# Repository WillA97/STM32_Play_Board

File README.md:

# STM32_Play_Board
 schematic of the microcontroller pcb files

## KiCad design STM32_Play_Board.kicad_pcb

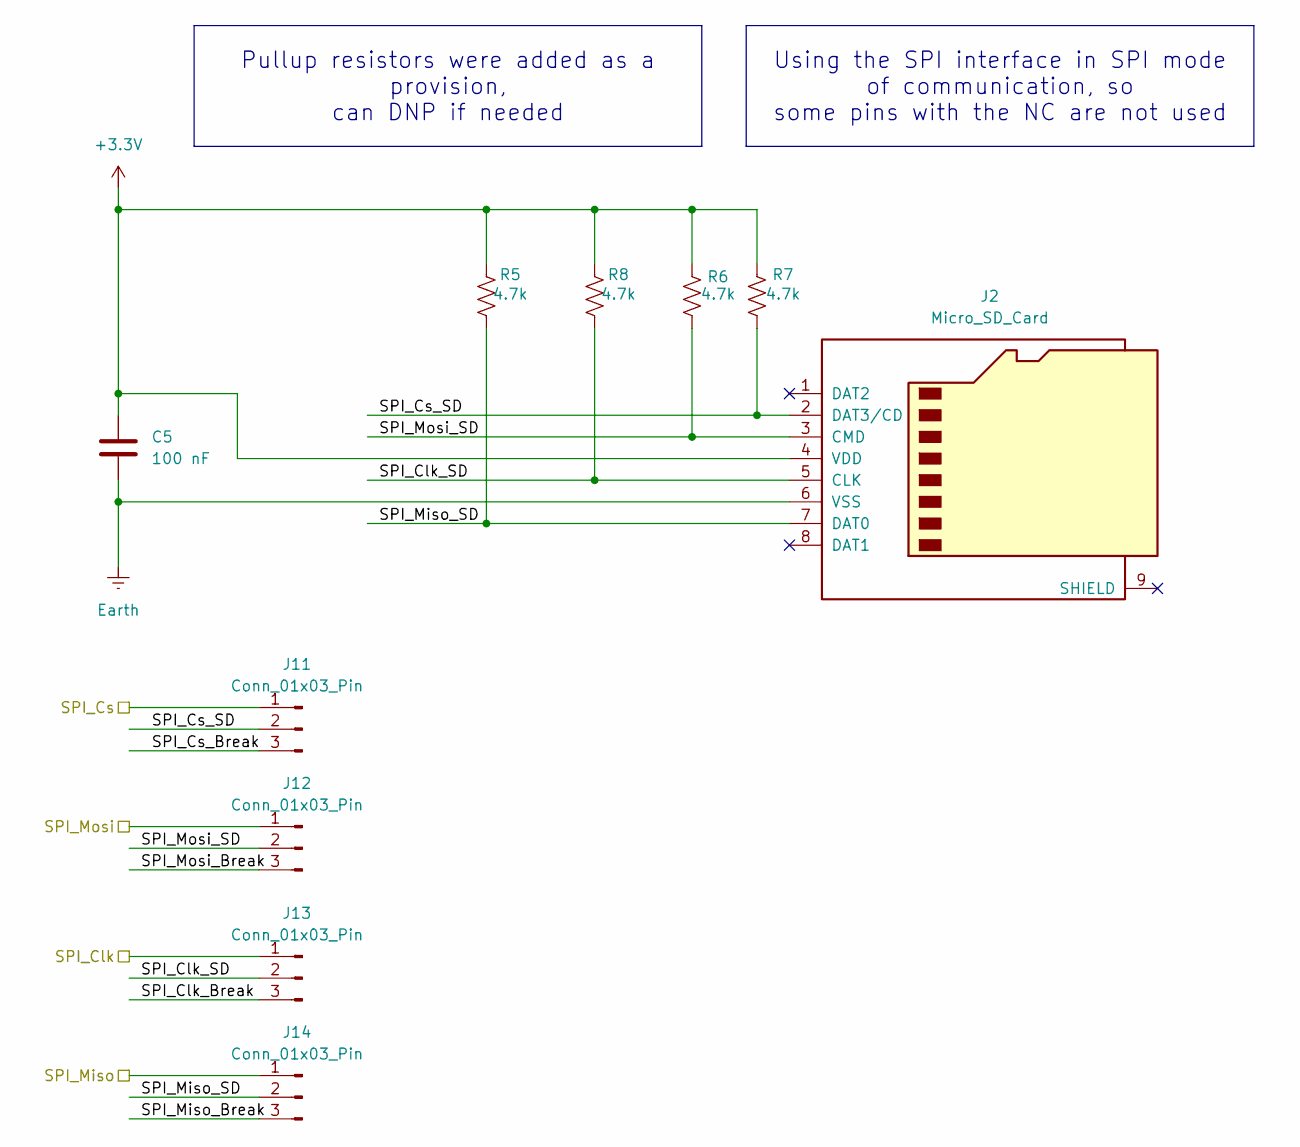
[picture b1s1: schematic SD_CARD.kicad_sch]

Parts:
C5: 100 nF; C_0805_2012Metric
J2: Micro_SD_Card; microSD_HC_Molex_104031-0811
J11, J12, J13, J14: Conn_01x03_Pin; PinHeader_1x03_P2.54mm_Vertical
R5, R6, R7, R8: 4.7k; R_0805_2012Metric

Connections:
+3.3V: C5.1, J2.4 (VDD), R5.1, R6.1, R7.1, R8.1; also elsewhere on the board
/Micrcontroller STM32C0/SPI_Clk: J13.1; also elsewhere on the board
/Micrcontroller STM32C0/SPI_Cs: J11.1; also elsewhere on the board
/Micrcontroller STM32C0/SPI_Miso: J14.1; also elsewhere on the board
/Micrcontroller STM32C0/SPI_Mosi: J12.1; also elsewhere on the board
/SD_CARD/SPI_Clk_Break: J13.3
/SD_CARD/SPI_Clk_SD: J2.5 (CLK), J13.2, R8.2
/SD_CARD/SPI_Cs_Break: J11.3
/SD_CARD/SPI_Cs_SD: J2.2 (DAT3/CD), J11.2, R7.2
/SD_CARD/SPI_Miso_Break: J14.3
/SD_CARD/SPI_Miso_SD: J2.7 (DAT0), J14.2, R5.2
/SD_CARD/SPI_Mosi_Break: J12.3
/SD_CARD/SPI_Mosi_SD: J2.3 (CMD), J12.2, R6.2
Earth: C5.2, J2.6 (VSS); also elsewhere on the board

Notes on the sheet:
Using the SPI interface in SPI mode of communication, so some pins with the NC are not used
Pullup resistors were added as a provision, can DNP if needed

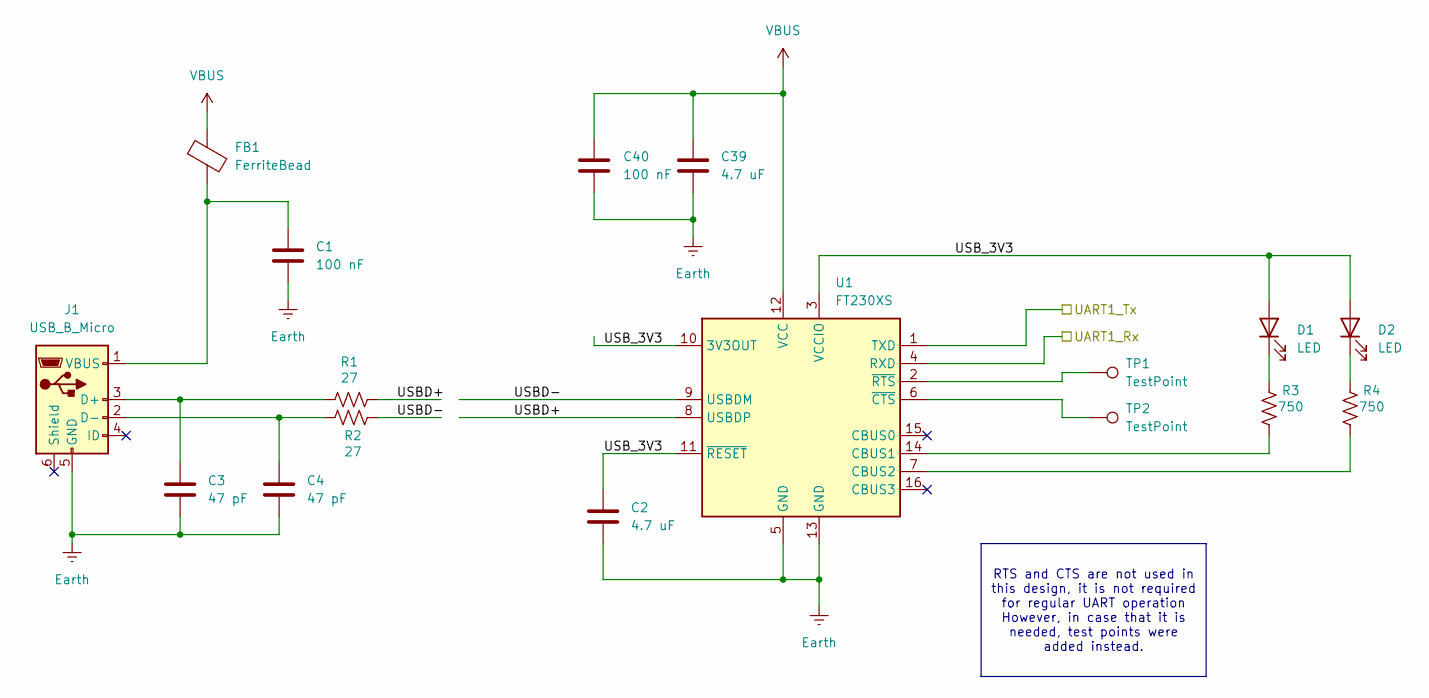
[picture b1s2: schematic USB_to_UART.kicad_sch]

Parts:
C1, C40: 100 nF; C_0805_2012Metric
C2, C39: 4.7 uF; C_0805_2012Metric
C3, C4: 47 pF; C_0805_2012Metric
D1, D2: LED; LED_0805_2012Metric
FB1: FerriteBead; L_0805_2012Metric
J1: USB_B_Micro; USB_Micro-B_Wuerth_629105150521
R1, R2: 27; R_0805_2012Metric
R3, R4: 750; R_0805_2012Metric
TP1, TP2: TestPoint; TestPoint_Pad_2.0x2.0mm
U1: FT230XS; SSOP-16_3.9x4.9mm_P0.635mm

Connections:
/Micrcontroller STM32C0/UART1_Rx: U1.4 (RXD); also elsewhere on the board
/Micrcontroller STM32C0/UART1_Tx: U1.1 (TXD); also elsewhere on the board
/USB to UART/USBD+: R1.2, U1.8 (USBDP)
/USB to UART/USBD-: R2.2, U1.9 (USBDM)
/USB to UART/USB_3V3: C2.1, D1.2 (A), D2.2 (A), U1.3 (VCCIO), U1.10 (3V3OUT), U1.11 (~RESET)
Earth: C1.2, C2.2, C3.2, C4.2, C39.2, C40.2, J1.5 (GND), U1.5 (GND), U1.13 (GND); also elsewhere on the board
unnamed: D1.1 (K), R3.1
unnamed: D2.1 (K), R4.1
unnamed: C3.1, J1.3 (D+), R1.1
unnamed: C4.1, J1.2 (D-), R2.1
unnamed: C1.1, FB1.2, J1.1 (VBUS)
unnamed: R3.2, U1.14 (CBUS1)
unnamed: R4.2, U1.7 (CBUS2)
unnamed: TP2.1, U1.6 (~CTS)
unnamed: TP1.1, U1.2 (~RTS)
VBUS: C39.1, C40.1, FB1.1, U1.12 (VCC); also elsewhere on the board

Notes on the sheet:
RTS and CTS are not used in this design, it is not required for regular UART operation However, in case that it is needed, test points were added instead.

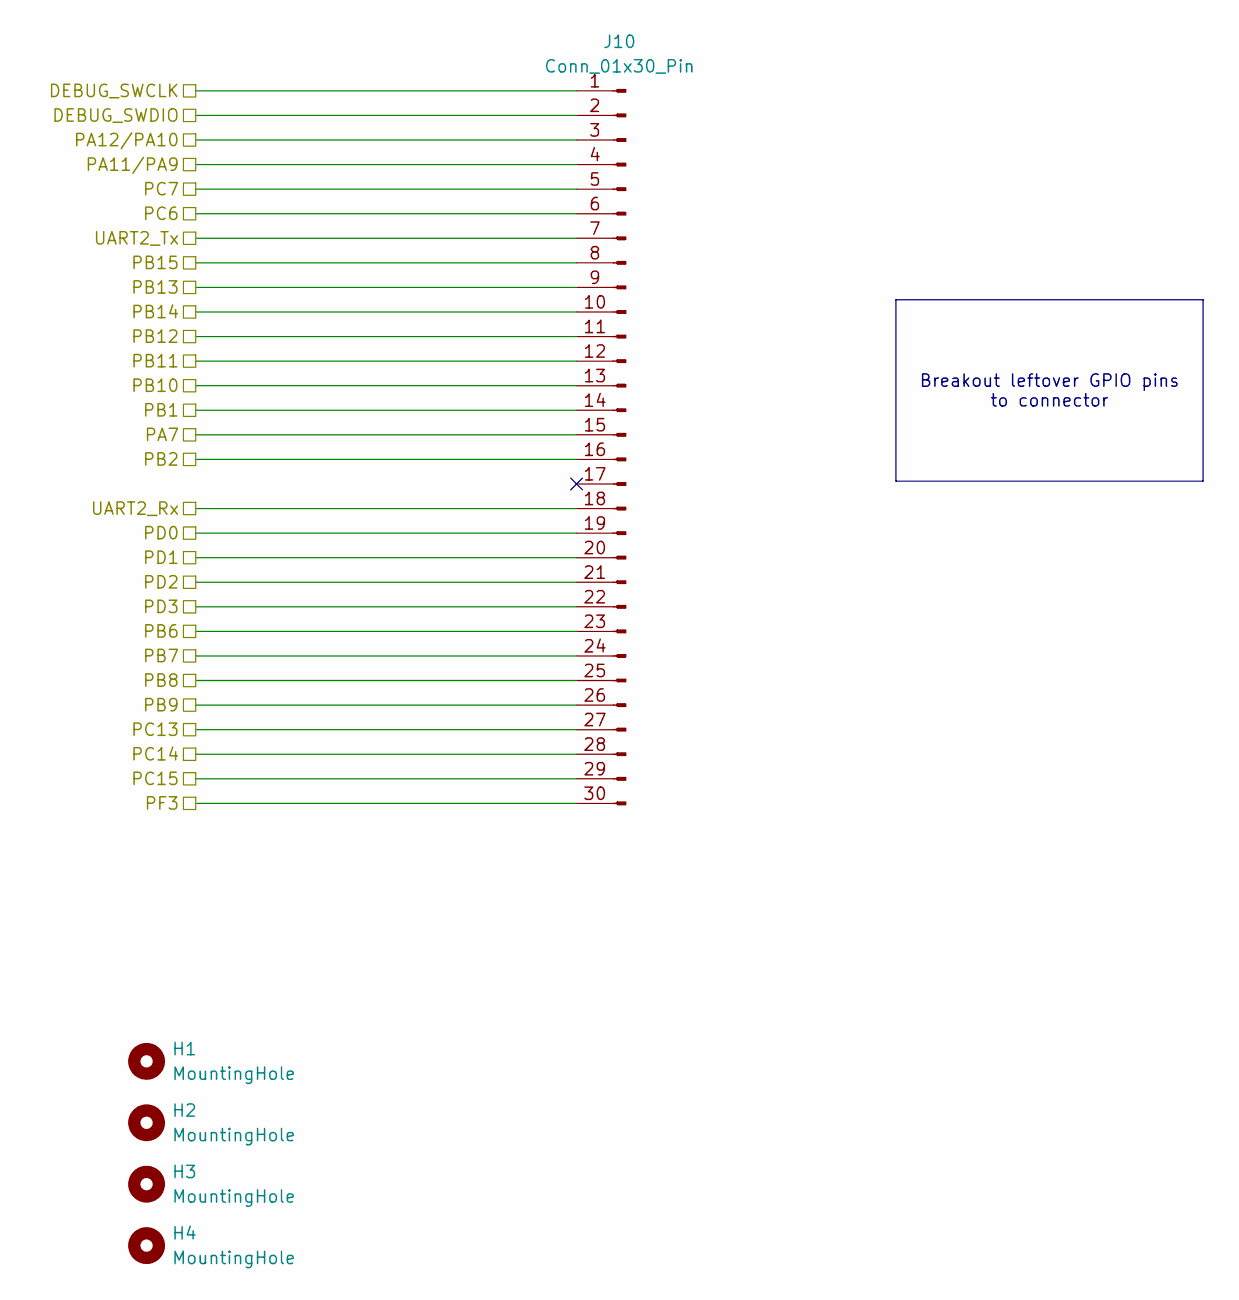
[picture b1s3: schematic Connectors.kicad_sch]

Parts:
H1, H2, H3, H4: MountingHole; MountingHole_3.2mm_M3
J10: Conn_01x30_Pin; PinHeader_1x30_P2.54mm_Vertical

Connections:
/Connectors/DEBUG_SWCLK: J10.1; also elsewhere on the board
/Connectors/DEBUG_SWDIO: J10.2; also elsewhere on the board
/Connectors/PA7: J10.15; also elsewhere on the board
/Connectors/PA11/PA9: J10.4; also elsewhere on the board
/Connectors/PA12/PA10: J10.3; also elsewhere on the board
/Connectors/PB1: J10.14; also elsewhere on the board
/Connectors/PB2: J10.16; also elsewhere on the board
/Connectors/PB6: J10.23; also elsewhere on the board
/Connectors/PB7: J10.24; also elsewhere on the board
/Connectors/PB8: J10.25; also elsewhere on the board
/Connectors/PB9: J10.26; also elsewhere on the board
/Connectors/PB10: J10.13; also elsewhere on the board
/Connectors/PB11: J10.12; also elsewhere on the board
/Connectors/PB12: J10.11; also elsewhere on the board
/Connectors/PB13: J10.9; also elsewhere on the board
/Connectors/PB14: J10.10; also elsewhere on the board
/Connectors/PB15: J10.8; also elsewhere on the board
/Connectors/PC6: J10.6; also elsewhere on the board
/Connectors/PC7: J10.5; also elsewhere on the board
/Connectors/PC13: J10.27; also elsewhere on the board
/Connectors/PC14: J10.28; also elsewhere on the board
/Connectors/PC15: J10.29; also elsewhere on the board
/Connectors/PD0: J10.19; also elsewhere on the board
/Connectors/PD1: J10.20; also elsewhere on the board
/Connectors/PD2: J10.21; also elsewhere on the board
/Connectors/PD3: J10.22; also elsewhere on the board
/Connectors/PF3: J10.30; also elsewhere on the board
/Micrcontroller STM32C0/UART2_Rx: J10.18; also elsewhere on the board
/Micrcontroller STM32C0/UART2_Tx: J10.7; also elsewhere on the board

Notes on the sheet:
Breakout leftover GPIO pins to connector

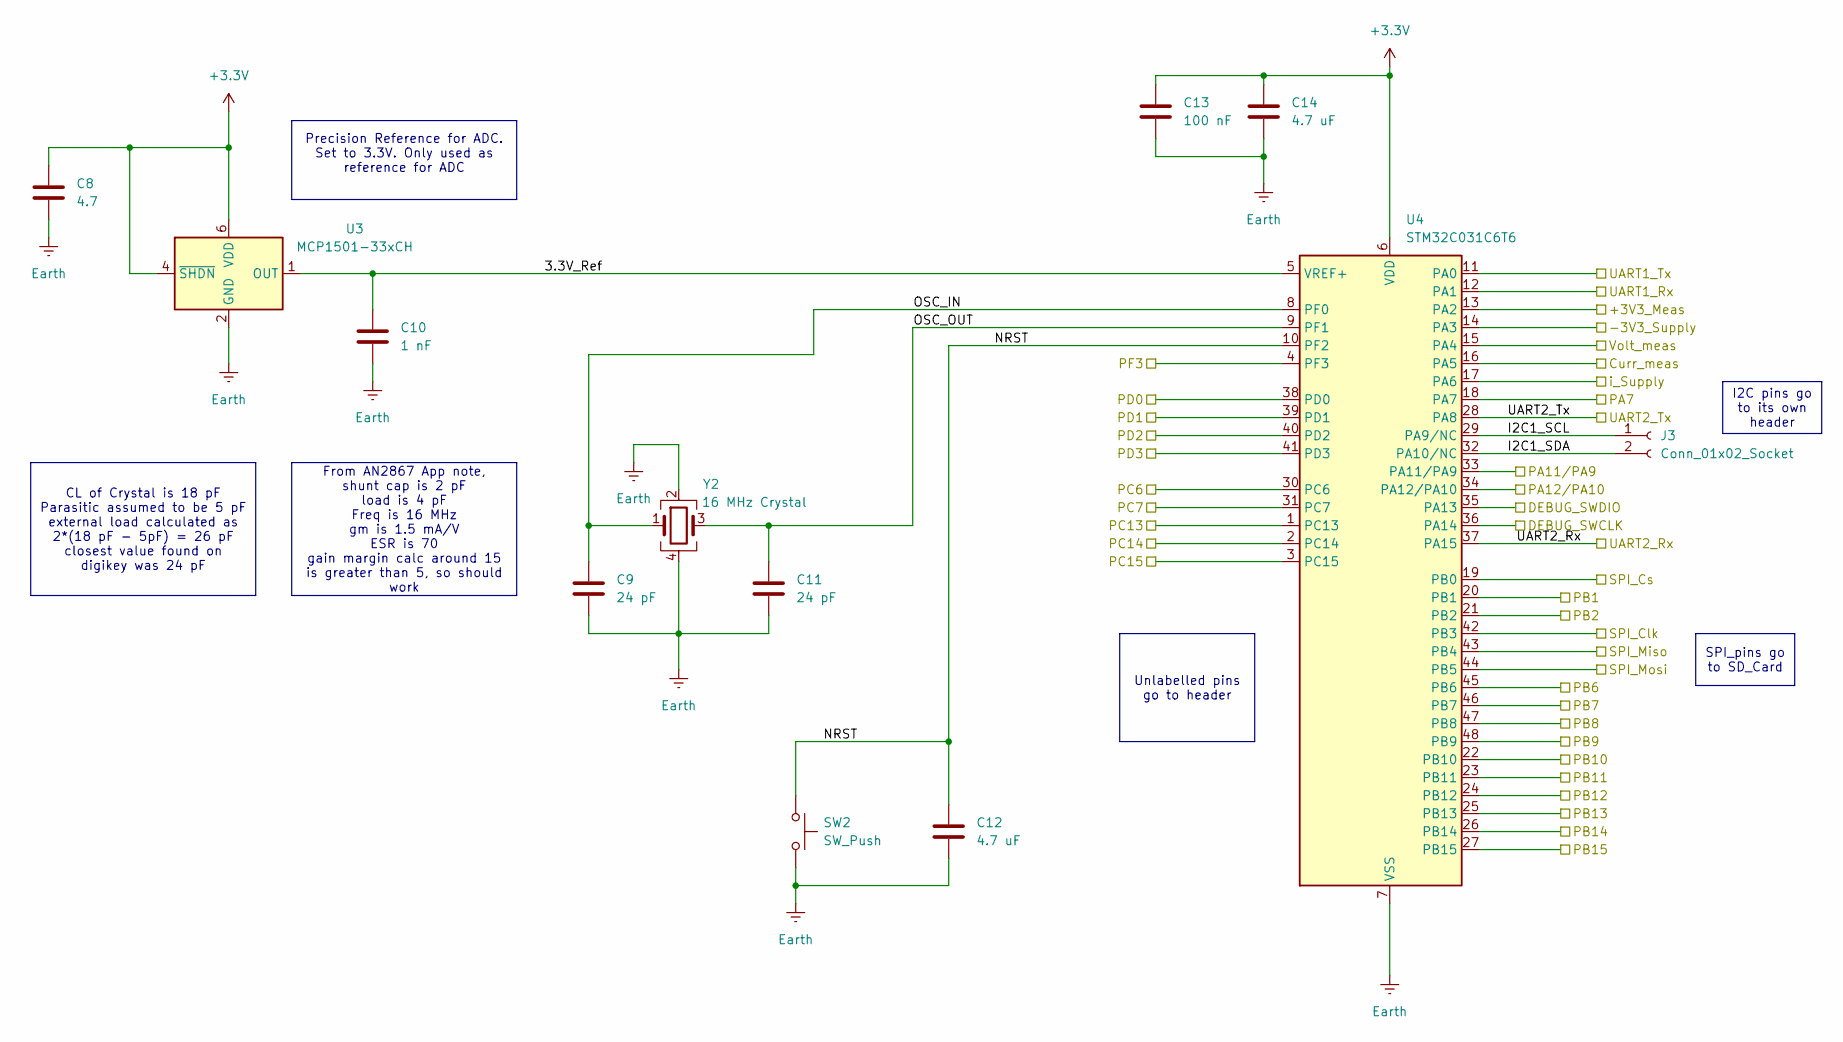
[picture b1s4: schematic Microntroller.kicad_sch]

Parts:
C8: 4.7; C_0805_2012Metric
C9, C11: 24 pF; C_0805_2012Metric
C10: 1 nF; C_0805_2012Metric
C12, C14: 4.7 uF; C_0805_2012Metric
C13: 100 nF; C_0805_2012Metric
J3: Conn_01x02_Socket; Molex_KK-254_AE-6410-02A_1x02_P2.54mm_Vertical
SW2: SW_Push; SW_PUSH_6mm
U3: MCP1501-33xCH; SOT-23-6
U4: STM32C031C6T6; LQFP-48_7x7mm_P0.5mm
Y2: 16 MHz Crystal; Oscillator_SMD_Abracon_ASE-4Pin_3.2x2.5mm_HandSoldering

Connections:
+3.3V: C8.1, C13.1, C14.1, U3.4 (~SHDN), U3.6 (VDD), U4.6 (VDD); also elsewhere on the board
/Connectors/DEBUG_SWCLK: U4.36 (PA14); also elsewhere on the board
/Connectors/DEBUG_SWDIO: U4.35 (PA13); also elsewhere on the board
/Connectors/PA7: U4.18 (PA7); also elsewhere on the board
/Connectors/PA11/PA9: U4.33 (PA11/PA9); also elsewhere on the board
/Connectors/PA12/PA10: U4.34 (PA12/PA10); also elsewhere on the board
/Connectors/PB1: U4.20 (PB1); also elsewhere on the board
/Connectors/PB2: U4.21 (PB2); also elsewhere on the board
/Connectors/PB6: U4.45 (PB6); also elsewhere on the board
/Connectors/PB7: U4.46 (PB7); also elsewhere on the board
/Connectors/PB8: U4.47 (PB8); also elsewhere on the board
/Connectors/PB9: U4.48 (PB9); also elsewhere on the board
/Connectors/PB10: U4.22 (PB10); also elsewhere on the board
/Connectors/PB11: U4.23 (PB11); also elsewhere on the board
/Connectors/PB12: U4.24 (PB12); also elsewhere on the board
/Connectors/PB13: U4.26 (PB14); also elsewhere on the board
/Connectors/PB14: U4.25 (PB13); also elsewhere on the board
/Connectors/PB15: U4.27 (PB15); also elsewhere on the board
/Connectors/PC6: U4.30 (PC6); also elsewhere on the board
/Connectors/PC7: U4.31 (PC7); also elsewhere on the board
/Connectors/PC13: U4.1 (PC13); also elsewhere on the board
/Connectors/PC14: U4.2 (PC14); also elsewhere on the board
/Connectors/PC15: U4.3 (PC15); also elsewhere on the board
/Connectors/PD0: U4.38 (PD0); also elsewhere on the board
/Connectors/PD1: U4.39 (PD1); also elsewhere on the board
/Connectors/PD2: U4.40 (PD2); also elsewhere on the board
/Connectors/PD3: U4.41 (PD3); also elsewhere on the board
/Connectors/PF3: U4.4 (PF3); also elsewhere on the board
/Micrcontroller STM32C0/3.3V_Ref: C10.1, U3.1 (OUT), U4.5 (VREF+)
/Micrcontroller STM32C0/+3V3_Meas: U4.13 (PA2); also elsewhere on the board
/Micrcontroller STM32C0/-3V3_Supply: U4.14 (PA3); also elsewhere on the board
/Micrcontroller STM32C0/Curr_meas: U4.16 (PA5); also elsewhere on the board
/Micrcontroller STM32C0/I2C1_SCL: J3.1, U4.29 (PA9/NC)
/Micrcontroller STM32C0/I2C1_SDA: J3.2, U4.32 (PA10/NC)
/Micrcontroller STM32C0/NRST: C12.1, SW2.1, U4.10 (PF2)
/Micrcontroller STM32C0/OSC_IN: C9.1, U4.8 (PF0), Y2.1
/Micrcontroller STM32C0/OSC_OUT: C11.1, U4.9 (PF1), Y2.3
/Micrcontroller STM32C0/SPI_Clk: U4.42 (PB3); also elsewhere on the board
/Micrcontroller STM32C0/SPI_Cs: U4.19 (PB0); also elsewhere on the board
/Micrcontroller STM32C0/SPI_Miso: U4.43 (PB4); also elsewhere on the board
/Micrcontroller STM32C0/SPI_Mosi: U4.44 (PB5); also elsewhere on the board
/Micrcontroller STM32C0/UART1_Rx: U4.12 (PA1); also elsewhere on the board
/Micrcontroller STM32C0/UART1_Tx: U4.11 (PA0); also elsewhere on the board
/Micrcontroller STM32C0/UART2_Rx: U4.37 (PA15); also elsewhere on the board
/Micrcontroller STM32C0/UART2_Tx: U4.28 (PA8); also elsewhere on the board
/Micrcontroller STM32C0/Volt_meas: U4.15 (PA4); also elsewhere on the board
/Micrcontroller STM32C0/i_Supply: U4.17 (PA6); also elsewhere on the board
Earth: C8.2, C9.2, C10.2, C11.2, C12.2, C13.2, C14.2, SW2.2, U3.2 (GND), U3.3 (GND), U3.5 (GND), U4.7 (VSS), Y2.2, Y2.4; also elsewhere on the board

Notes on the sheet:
Precision Reference for ADC. Set to 3.3V. Only used as reference for ADC
Unlabelled pins go to header
I2C pins go to its own header
CL of Crystal is 18 pF Parasitic assumed to be 5 pF external load calculated as 2*(18 pF - 5pF) = 26 pF closest value found on digikey was 24 pF
From AN2867 App note, shunt cap is 2 pF load is 4 pF Freq is 16 MHz gm is 1.5 mA/V ESR is 70 gain margin calc around 15 is greater than 5, so should work
SPI_pins go to SD_Card

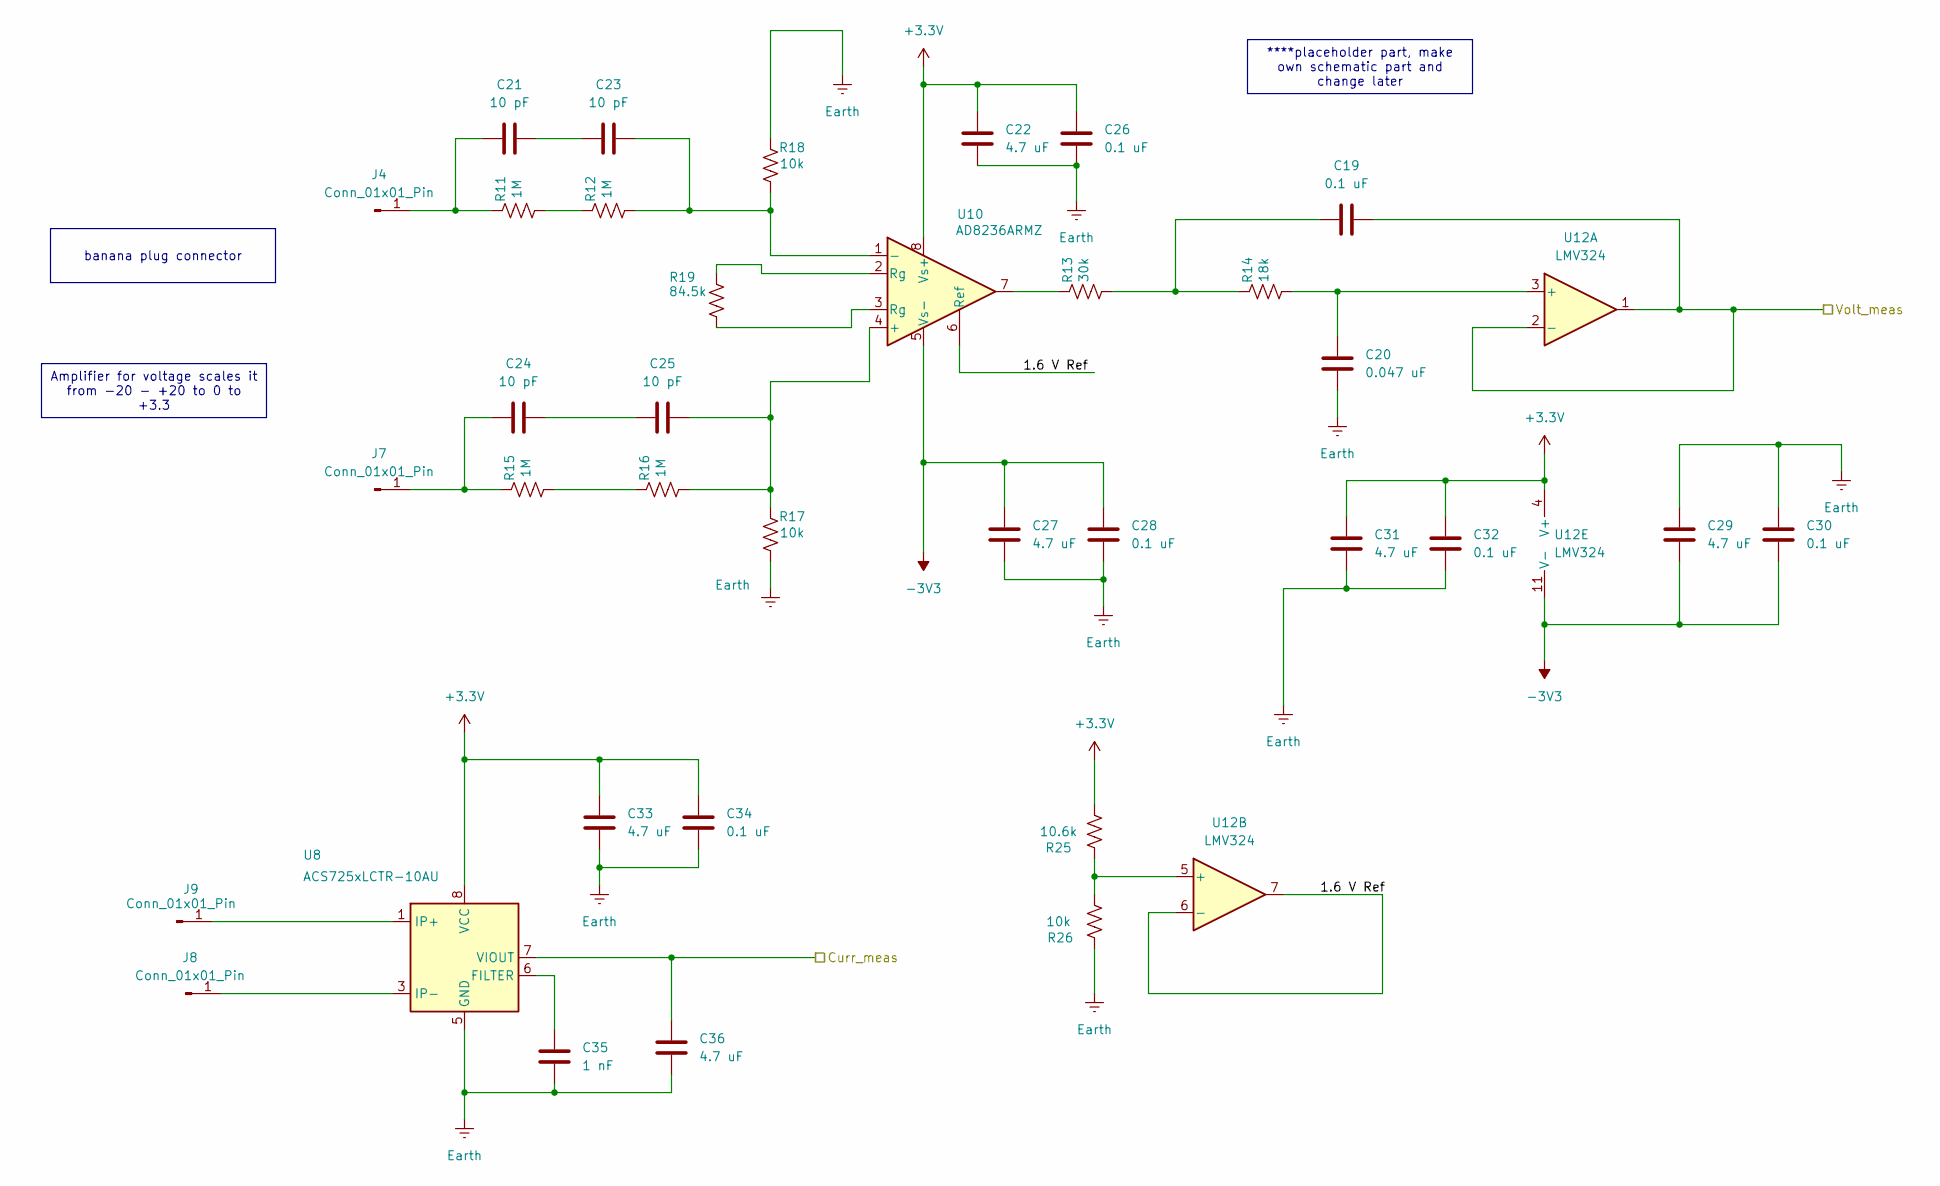
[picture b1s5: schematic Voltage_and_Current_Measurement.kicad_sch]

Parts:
C19, C26, C28, C30, C32, C34: 0.1 uF; C_0805_2012Metric
C20: 0.047 uF; C_0805_2012Metric
C21, C23, C24, C25: 10 pF; C_0805_2012Metric
C22, C27, C29, C31, C33, C36: 4.7 uF; C_0805_2012Metric
C35: 1 nF; C_0805_2012Metric
J4, J7, J8, J9: Conn_01x01_Pin; Banana_Jack_1Pin
R11, R12, R15, R16: 1M; R_0805_2012Metric
R13: 30k; R_0805_2012Metric
R14: 18k; R_0805_2012Metric
R17, R18, R26: 10k; R_0805_2012Metric
R19: 84.5k; R_0805_2012Metric
R25: 10.6k; R_0805_2012Metric
U8: ACS725xLCTR-10AU; SOIC-8_3.9x4.9mm_P1.27mm
U10: AD8236ARMZ; MSOP-8_3x3mm_P0.65mm
U12: LMV324; SOIC-14_3.9x8.7mm_P1.27mm_STM32_Play

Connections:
+3.3V: C22.2, C26.2, C31.2, C32.2, C33.2, C34.2, R25.2, U8.8 (VCC), U10.8 (Vs+), U12.4 (V+); also elsewhere on the board
-3V3: C27.2, C28.2, C29.1, C30.1, U10.5 (Vs-), U12.11 (V-); also elsewhere on the board
/Micrcontroller STM32C0/Curr_meas: C36.2, U8.7 (VIOUT); also elsewhere on the board
/Micrcontroller STM32C0/Volt_meas: C19.2, U12.1, U12.2 (-); also elsewhere on the board
/Voltage and Current Measurement/1.6 V Ref: U10.6 (Ref), U12.6 (-), U12.7
Earth: C20.1, C22.1, C26.1, C27.1, C28.1, C29.2, C30.2, C31.1, C32.1, C33.1, C34.1, C35.1, C36.1, R17.2, R18.1, R26.1, U8.5 (GND); also elsewhere on the board
unnamed: C19.1, R13.2, R14.1
unnamed: C21.2, C23.1
unnamed: C24.2, C25.1
unnamed: C21.1, J4.1, R11.1
unnamed: C24.1, J7.1, R15.1
unnamed: J8.1, U8.3 (IP-), U8.4 (IP-)
unnamed: J9.1, U8.1 (IP+), U8.2 (IP+)
unnamed: R11.2, R12.1
unnamed: R13.1, U10.7
unnamed: R15.2, R16.1
unnamed: R19.1, U10.2 (Rg)
unnamed: R19.2, U10.3 (Rg)
unnamed: C35.2, U8.6 (FILTER)
unnamed: C25.2, R16.2, R17.1, U10.4 (+)
unnamed: C23.2, R12.2, R18.2, U10.1 (-)
unnamed: C20.2, R14.2, U12.3 (+)
unnamed: R25.1, R26.2, U12.5 (+)

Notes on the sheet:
Amplifier for voltage scales it from -20 - +20 to 0 to +3.3
****placeholder part, make own schematic part and change later
banana plug connector

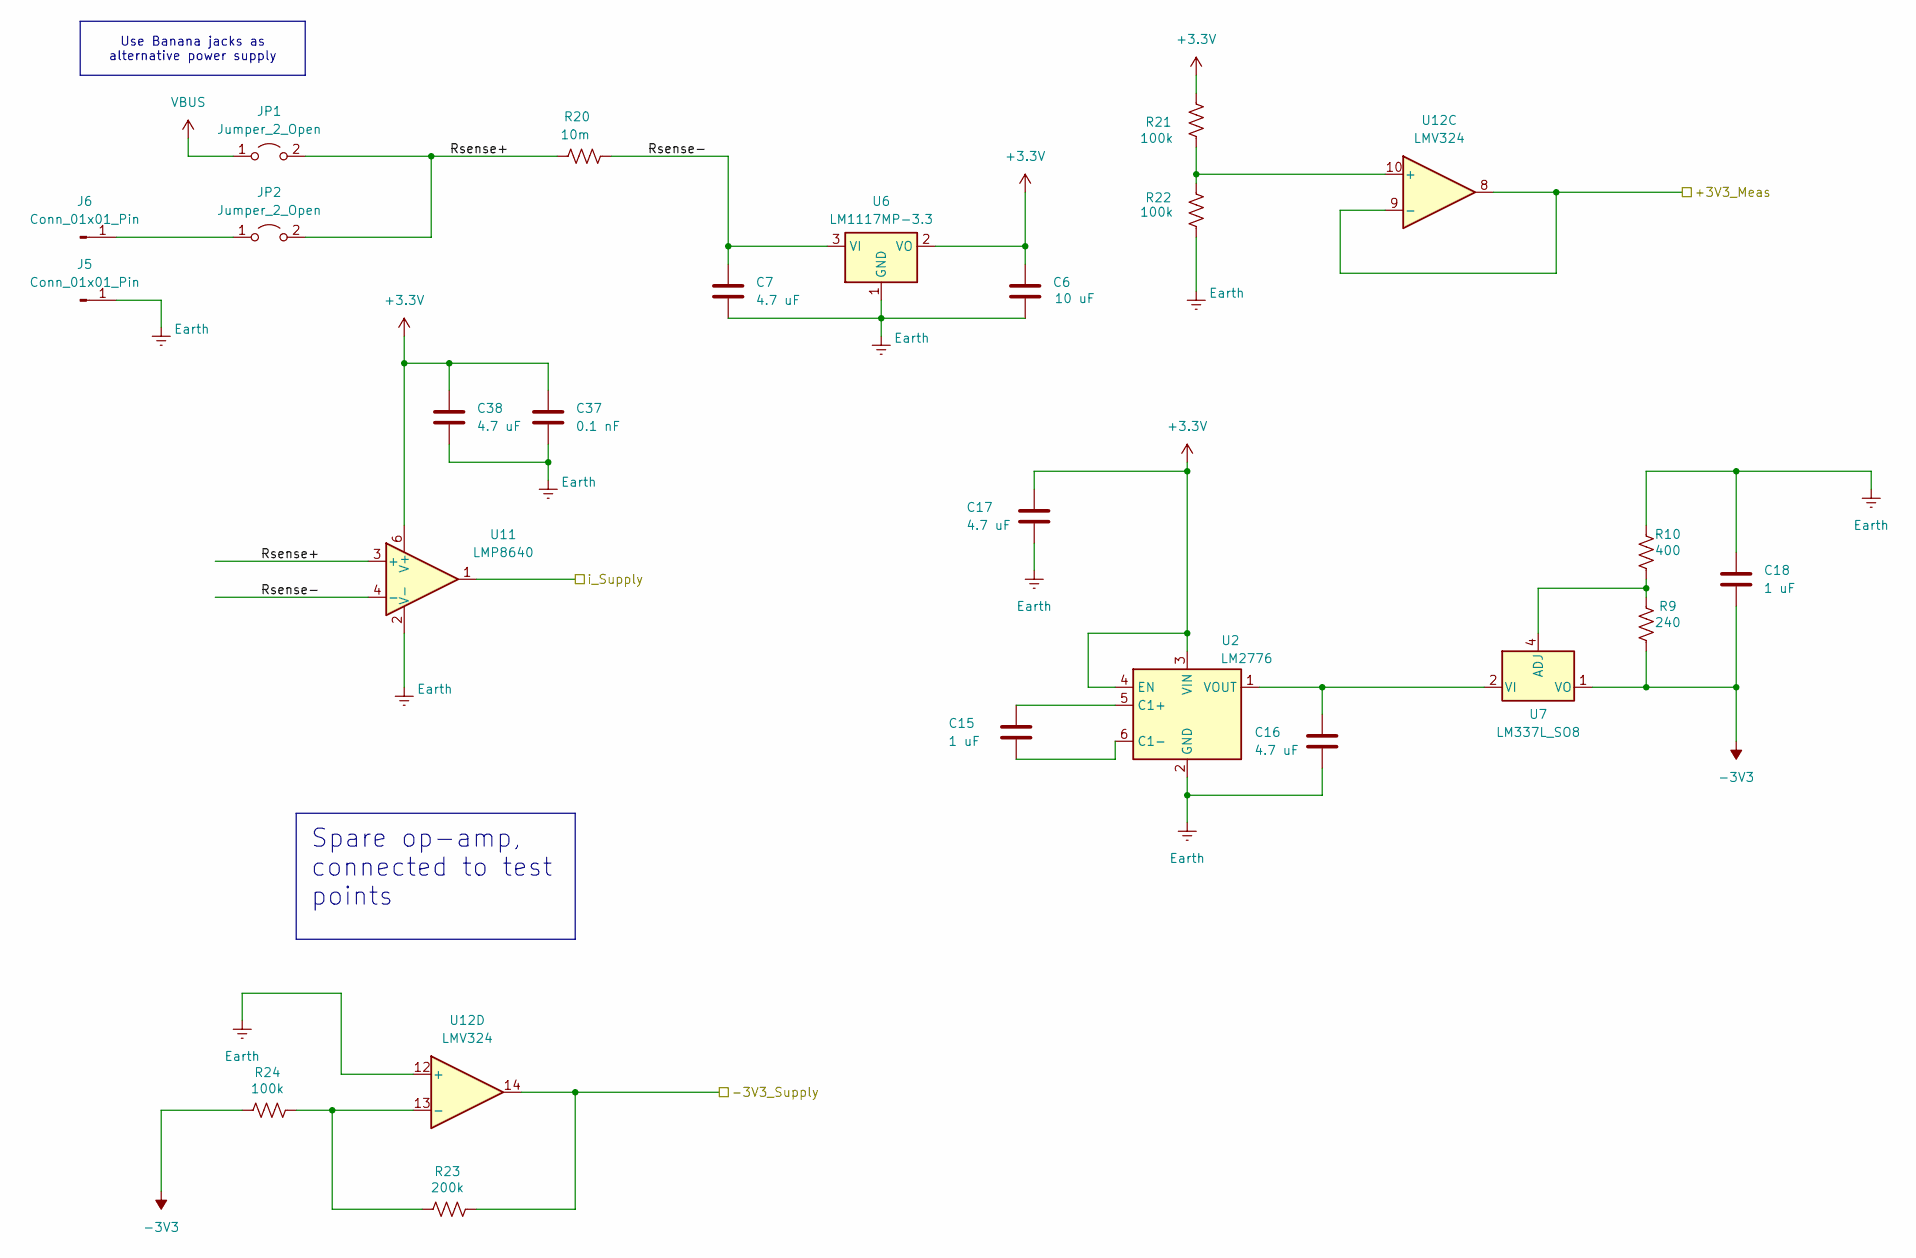
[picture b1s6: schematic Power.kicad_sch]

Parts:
C6: 10 uF; C_0805_2012Metric
C7, C16, C17, C38: 4.7 uF; C_0805_2012Metric
C15, C18: 1 uF; C_0805_2012Metric
C37: 0.1 nF; C_0805_2012Metric
J5: Conn_01x01_Pin; TestPoint_THTPad_D1.5mm_Drill0.7mm
J6: Conn_01x01_Pin; TestPoint_THTPad_1.5x1.5mm_Drill0.7mm
JP1, JP2: Jumper_2_Open; PinHeader_1x02_P2.54mm_Vertical
R9: 240; R_0805_2012Metric
R10: 400; R_0805_2012Metric
R20: 10m; R_0805_2012Metric
R21, R22, R24: 100k; R_0805_2012Metric
R23: 200k; R_0805_2012Metric
U2: LM2776; SOT-23-6
U6: LM1117MP-3.3; SOT-223-3_TabPin2
U7: LM337L_SO8; SOIC-8_3.9x4.9mm_P1.27mm
U11: LMP8640; SOT-23-6
U12: LMV324; SOIC-14_3.9x8.7mm_P1.27mm_STM32_Play

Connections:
+3.3V: C6.1, C17.1, C37.1, C38.1, R21.2, U2.3 (VIN), U2.4 (EN), U6.2 (VO), U11.6 (V+); also elsewhere on the board
-3V3: C18.2, R9.2, R24.1, U7.1 (VO); also elsewhere on the board
/Micrcontroller STM32C0/+3V3_Meas: U12.8, U12.9 (-); also elsewhere on the board
/Micrcontroller STM32C0/-3V3_Supply: R23.2, U12.14; also elsewhere on the board
/Micrcontroller STM32C0/i_Supply: U11.1; also elsewhere on the board
/Power/Rsense+: JP1.2 (B), JP2.2 (B), R20.1, U11.3 (+)
/Power/Rsense-: C7.1, R20.2, U6.3 (VI), U11.4 (-)
Earth: C6.2, C7.2, C16.2, C17.2, C18.1, C37.2, C38.2, J5.1, R10.1, R22.1, U2.2 (GND), U6.1 (GND), U11.2 (V-), U12.12 (+); also elsewhere on the board
unnamed: J6.1, JP2.1 (A)
unnamed: C15.1, U2.5 (C1+)
unnamed: C15.2, U2.6 (C1-)
unnamed: C16.1, U2.1 (VOUT), U7.2 (VI), U7.3 (VI), U7.6 (VI), U7.7 (VI)
unnamed: R9.1, R10.2, U7.4 (ADJ)
unnamed: R21.1, R22.2, U12.10 (+)
unnamed: R23.1, R24.2, U12.13 (-)
VBUS: JP1.1 (A); also elsewhere on the board

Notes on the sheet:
Spare op-amp, connected to test points
Use Banana jacks as alternative power supply

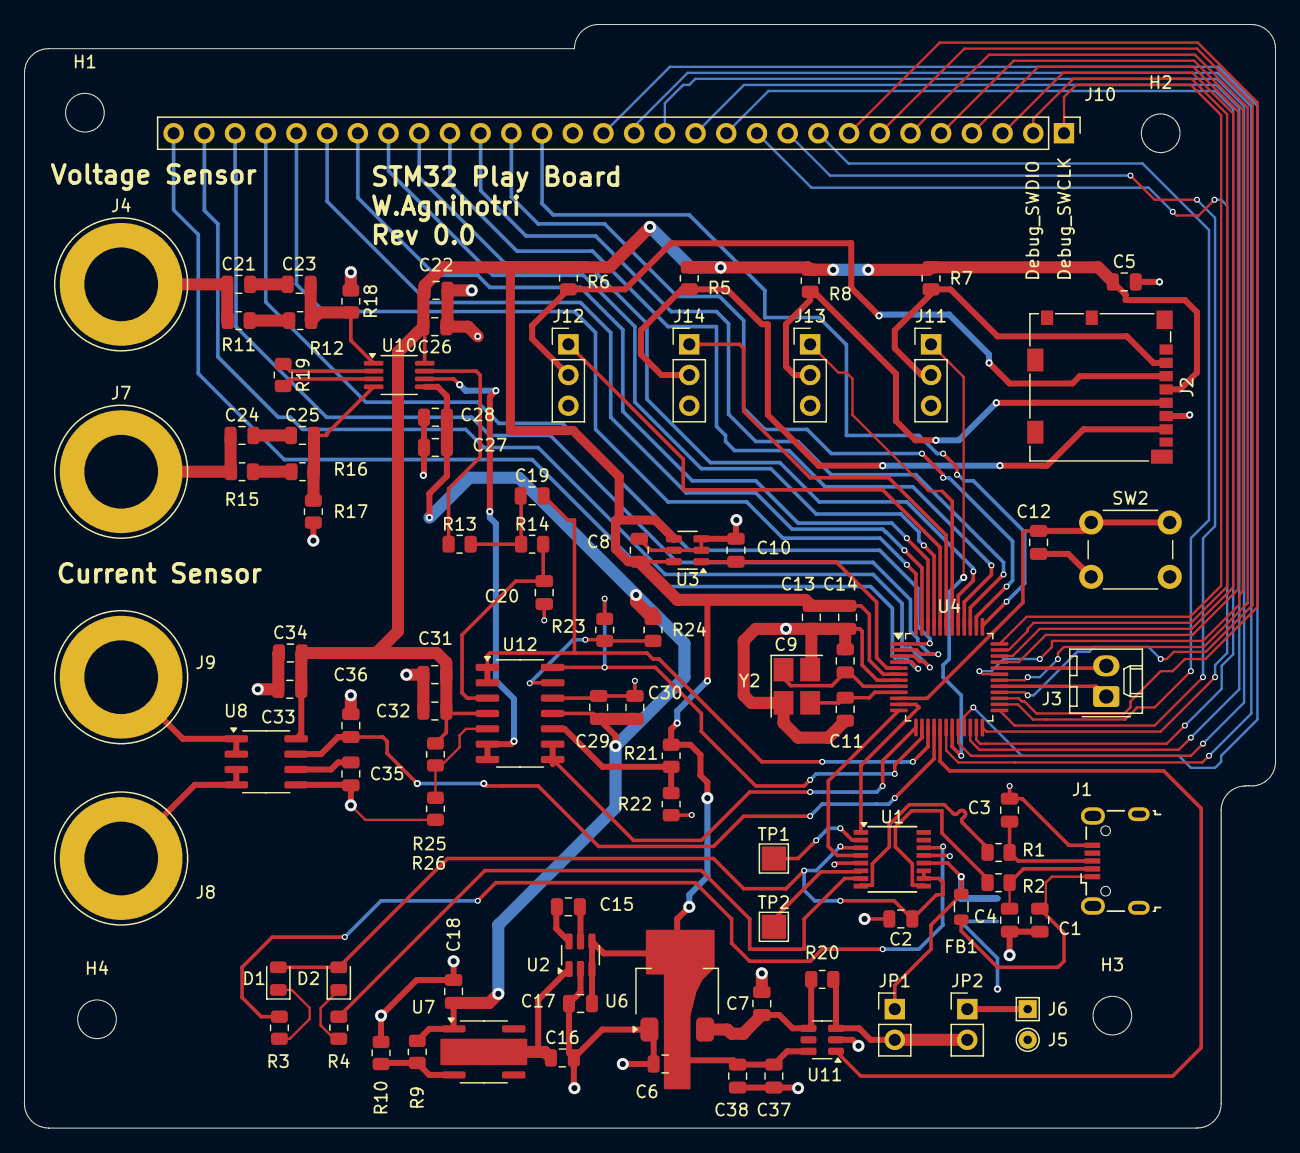
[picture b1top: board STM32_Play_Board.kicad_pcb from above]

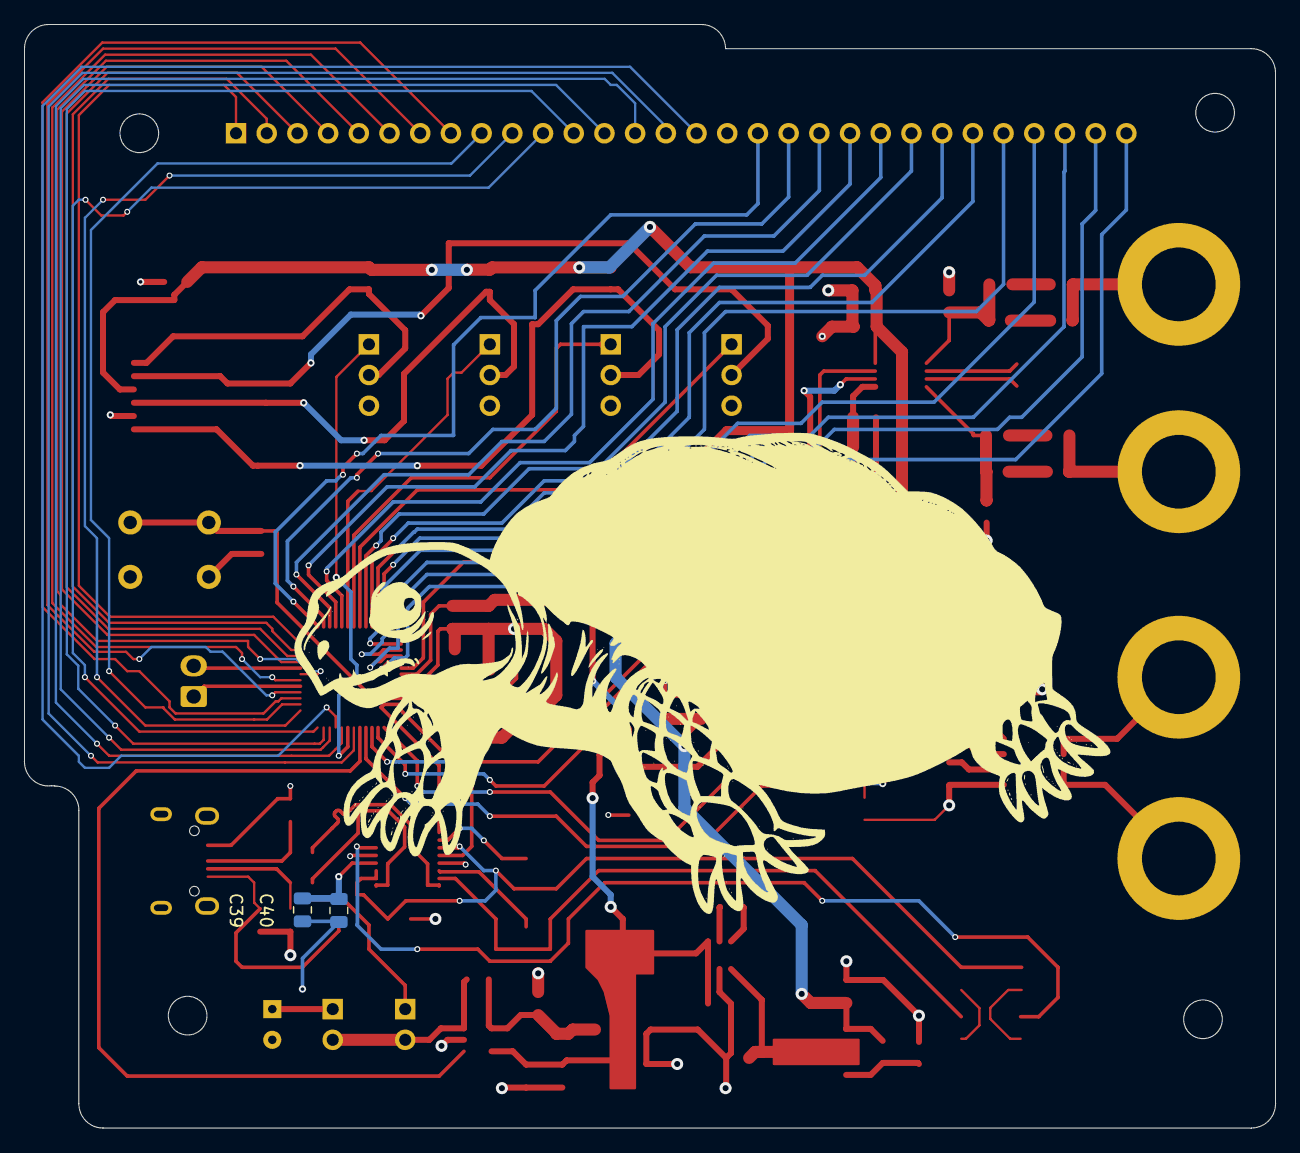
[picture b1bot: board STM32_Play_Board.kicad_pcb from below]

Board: 4 copper layers, 103.5 x 91.3 mm, 103 parts (2 on the bottom side), 93 nets.

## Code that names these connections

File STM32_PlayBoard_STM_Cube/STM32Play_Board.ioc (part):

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Mcu.Name=STM32C031C(4-6)Tx
Mcu.Package=LQFP48
Mcu.UserName=STM32C031C6Tx
PA0.Mode=Asynchronous
PA0.Signal=USART1_TX
PA1.Mode=Asynchronous
PA1.Signal=USART1_RX
PA10.Mode=I2C
PA10.Signal=I2C1_SDA
PA13.Mode=Serial_Wire
PA13.Signal=DEBUG_SWDIO
PA14-BOOT0.Mode=Serial_Wire
PA14-BOOT0.Signal=DEBUG_SWCLK
PA15.Mode=Asynchronous
PA15.Signal=USART2_RX
PA2.Mode=IN2
PA2.Signal=ADC1_IN2
PA3.Mode=IN3
PA3.Signal=ADC1_IN3
PA4.Mode=IN4
PA4.Signal=ADC1_IN4
PA5.Mode=IN5
PA5.Signal=ADC1_IN5
PA6.Mode=IN6
PA6.Signal=ADC1_IN6
PA8.Mode=Asynchronous
PA8.Signal=USART2_TX
PA9.Mode=I2C
PA9.Signal=I2C1_SCL
PB0.Mode=NSS_Signal_Hard_Output
PB0.Signal=SPI1_NSS
PB3.Mode=Full_Duplex_Master
PB3.Signal=SPI1_SCK
PB4.Mode=Full_Duplex_Master
PB4.Signal=SPI1_MISO
PB5.Mode=Full_Duplex_Master
PB5.Signal=SPI1_MOSI
PC14-OSCX_IN\ (PC14).Mode=HSE-External-Oscillator-REMAPPED
PC14-OSCX_IN\ (PC14).Signal=RCC_OSCX_IN
PC15-OSCX_OUT\ (PC15).Mode=HSE-External-Oscillator-REMAPPED
PC15-OSCX_OUT\ (PC15).Signal=RCC_OSCX_OUT
PC6.Signal=S_TIM3_CH1
PF3.Signal=GPIO_Output
RCC.HSE_VALUE=16000000
RCC.SYSCLKFreq_VALUE=16000000
RCC.SYSCLKSource=RCC_SYSCLKSOURCE_HSE
board=custom

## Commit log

2024-04-07 added components and schematics
2024-04-08 added power components
2024-04-11 dfvdfv
2024-04-14 added voltage measurement and current measurement
2024-04-22 updated schematics added the stm cube project file
2024-05-02 changes to schematic and PCB
2024-05-13 changed schematics
2024-05-20 changes to schematic
2024-06-03 random changes
2024-06-10 development
2024-08-05 m,vm
    not sure what changes are made lol
2024-09-06 bunch_of_changes_forgot
